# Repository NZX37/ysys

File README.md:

# YouSnoozeYouSolve Clock

### Inspiration

I wanted to create an alarm clock, right now i rely on my phone and i always end up snoozing until I am late. Other times my alarm wakes me up but it is so easy to snooze, its one button. So i thought why not make snoozing a pain while also "waking" me up?

### Description

The clock features a numberpad, screen and buzzer. The screen shows the time which is updated with wifi when available and internally counted when not connected. You can set alarms which force you to answer math questions to stop the alarm. The case has a glasses holder and watch stand (multifunctionality!!)

### Specifications

BOM: 
- 9x Cherry MX Switches
- 1x XIAO ESP32 C3
- 9x Blank DSA Keycaps
- 8x M3x8 Bolt
- 8x M3 Heatset
- 12x Through-Hole 1N4148 Diodes
-1x 2.25in TFT Screen
-1x 3.3V Piezo Buzzer
-1x 2.54mm 8 Pin Male Header
-8x 20cm Female-Female Jumper Wires

Others:
- Top Case.stl
- Middle Case.stl
- BLAREysys.ino
- Bottom Case.stl

Schematic            |  PCB         |   Case
:-------------------------:|:-------------------------:|:-------------------------:|
 |  |

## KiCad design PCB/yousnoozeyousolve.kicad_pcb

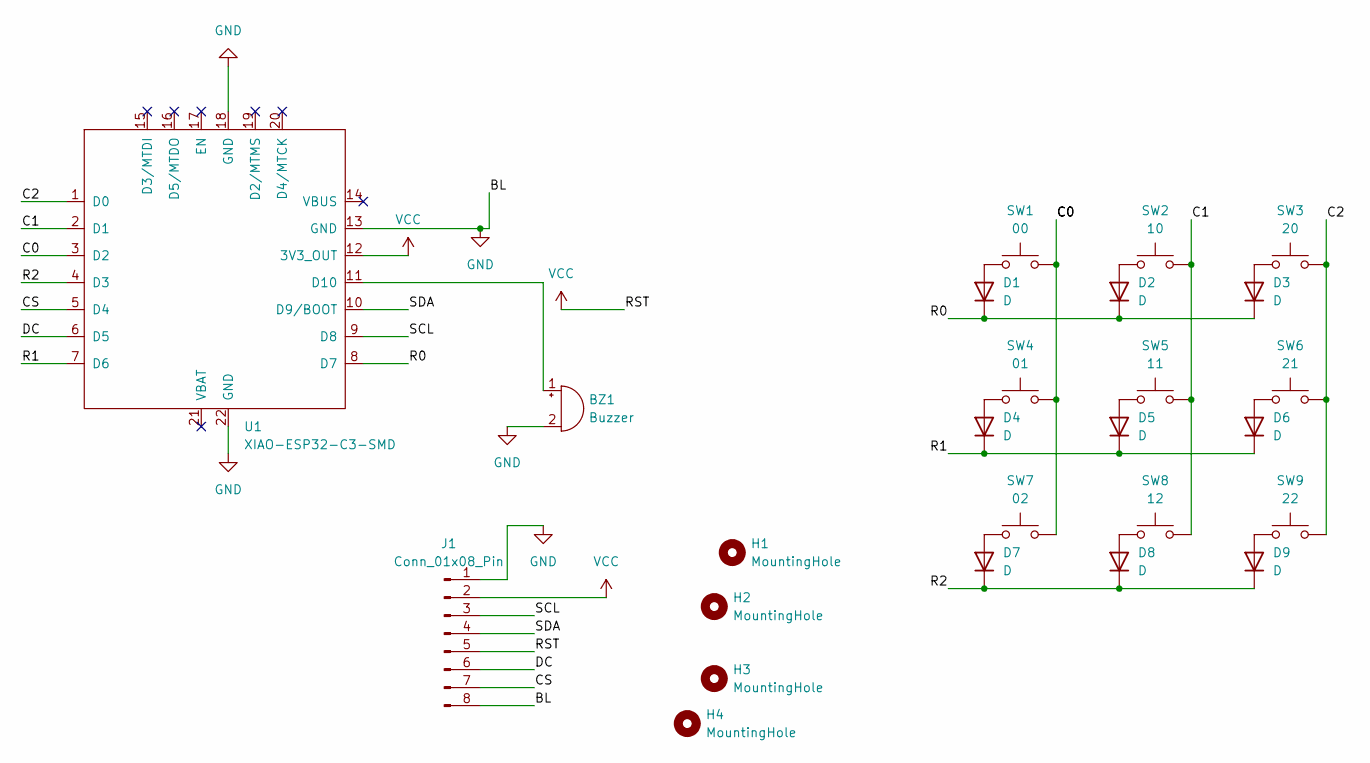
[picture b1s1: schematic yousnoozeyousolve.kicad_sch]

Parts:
BZ1: Buzzer; Buzzer_12x9.5RM7.6
D1, D2, D3, D4, D5, D6, D7, D8, D9: D; D_DO-35_SOD27_P7.62mm_Horizontal
H1, H2, H3, H4: MountingHole; MountingHole_3.2mm_M3
J1: Conn_01x08_Pin; PinSocket_1x08_P2.54mm_Vertical
SW1: 00; SW_Cherry_MX_1.00u_PCB
SW2: 10; SW_Cherry_MX_1.00u_PCB
SW3: 20; SW_Cherry_MX_1.00u_PCB
SW4: 01; SW_Cherry_MX_1.00u_PCB
SW5: 11; SW_Cherry_MX_1.00u_PCB
SW6: 21; SW_Cherry_MX_1.00u_PCB
SW7: 02; SW_Cherry_MX_1.00u_PCB
SW8: 12; SW_Cherry_MX_1.00u_PCB
SW9: 22; SW_Cherry_MX_1.00u_PCB
U1: XIAO-ESP32-C3-SMD; XIAO-ESP32-C3-DIP

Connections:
/C0: SW1.2, SW4.2, SW7.2, U1.3 (D2)
/C1: SW2.2, SW5.2, SW8.2, U1.2 (D1)
/C2: SW3.2, SW6.2, SW9.2, U1.1 (D0)
/CS: J1.7, U1.5 (D4)
/DC: J1.6, U1.6 (D5)
/R0: D1.1 (K), D2.1 (K), D3.1 (K), U1.8 (D7)
/R1: D4.1 (K), D5.1 (K), D6.1 (K), U1.7 (D6)
/R2: D7.1 (K), D8.1 (K), D9.1 (K), U1.4 (D3)
/SCL: J1.3, U1.9 (D8)
/SDA: J1.4, U1.10 (D9/BOOT)
GND: BZ1.2 (-), J1.1, J1.8, U1.13 (GND), U1.18 (GND), U1.22 (GND)
unnamed: BZ1.1 (+), U1.11 (D10)
unnamed: D1.2 (A), SW1.1
unnamed: D2.2 (A), SW2.1
unnamed: D3.2 (A), SW3.1
unnamed: D4.2 (A), SW4.1
unnamed: D5.2 (A), SW5.1
unnamed: D6.2 (A), SW6.1
unnamed: D7.2 (A), SW7.1
unnamed: D8.2 (A), SW8.1
unnamed: D9.2 (A), SW9.1
VCC: J1.2, J1.5, U1.12 (3V3_OUT)

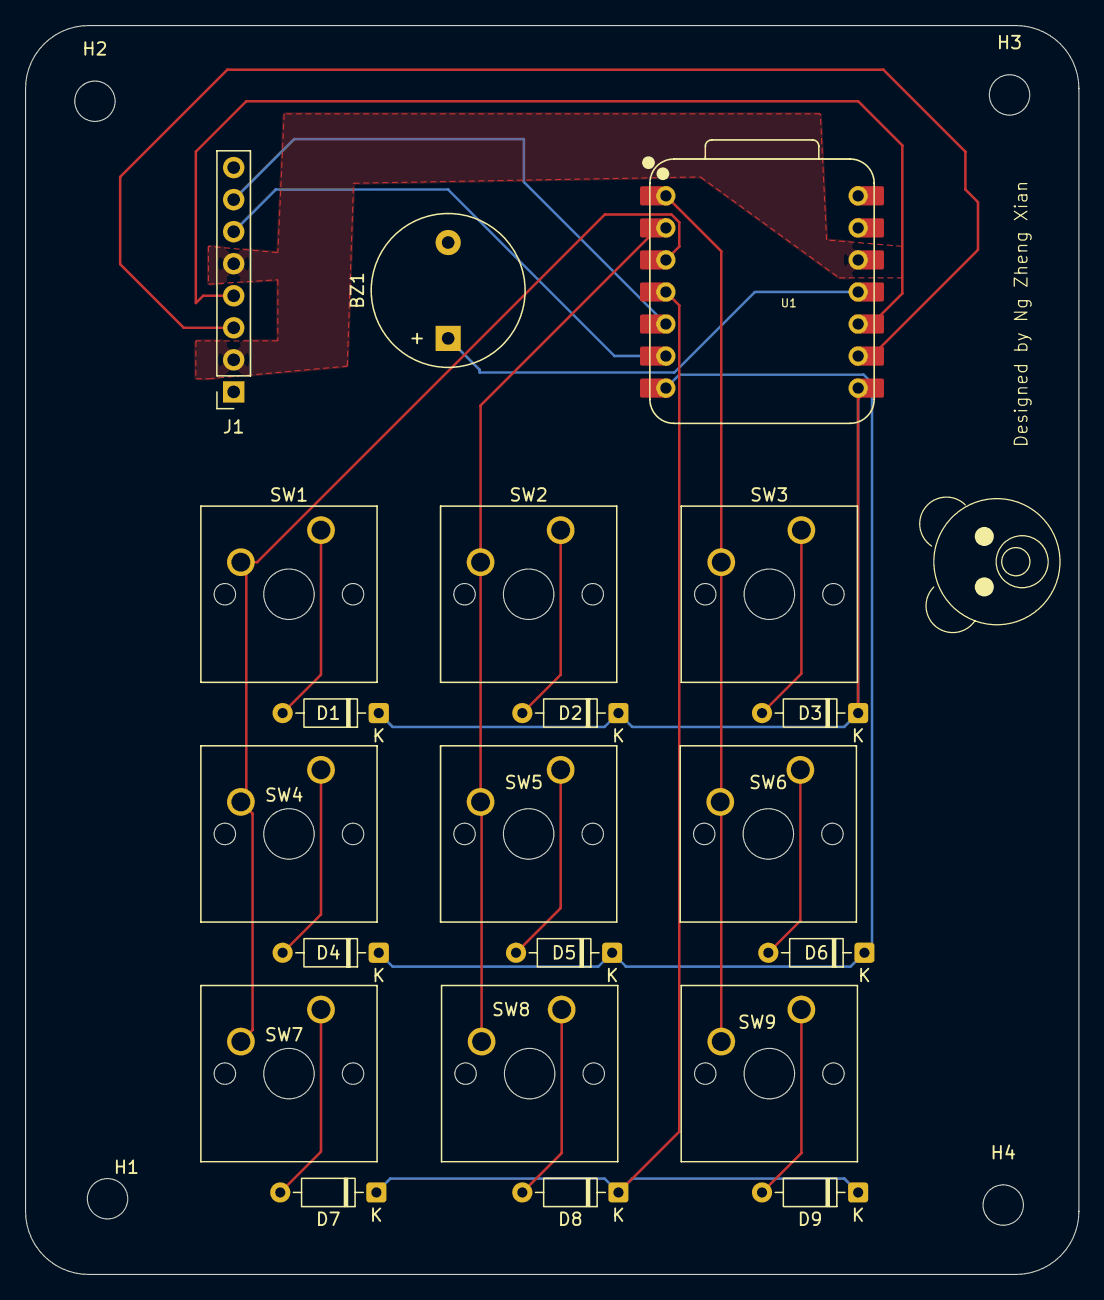
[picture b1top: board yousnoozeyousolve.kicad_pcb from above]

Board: 2 copper layers, 83.5 x 99.0 mm, 25 parts (0 on the bottom side), 22 nets.

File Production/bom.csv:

Designator,Footprint,Quantity,Value,LCSC Part #
BZ1,Buzzer_12x9.5RM7.6,1,Buzzer,
"D1, D2, D3, D4, D5, D6, D7, D8, D9",D_DO-35_SOD27_P7.62mm_Horizontal,9,D,
J1,PinSocket_1x08_P2.54mm_Vertical,1,Conn_01x08_Pin,
SW10,SW_Cherry_MX_1.00u_PCB,1,00,
SW11,SW_Cherry_MX_1.00u_PCB,1,01,
SW12,SW_Cherry_MX_1.00u_PCB,1,02,
SW13,SW_Cherry_MX_1.00u_PCB,1,10,
SW14,SW_Cherry_MX_1.00u_PCB,1,11,
SW15,SW_Cherry_MX_1.00u_PCB,1,12,
SW16,SW_Cherry_MX_1.00u_PCB,1,20,
SW17,SW_Cherry_MX_1.00u_PCB,1,21,
SW18,SW_Cherry_MX_1.00u_PCB,1,22,
U1,XIAO-ESP32-C3-DIP,1,XIAO-ESP32-C3-SMD,
